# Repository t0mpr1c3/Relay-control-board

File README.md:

Relay-control-board
===================

Control board for NAIS JSM1A or Songle SRD NO relays on Dangerous Prototypes DP5031 standard PCB size.

Derived from Sparkfun Electronics COM-11041 designed by N. Seidle and Joel Bartlett.

The component values are designed for VCC = 5 VDC. For VCC = 12 VDC, use R2 = 2.2K and R4 = 3.3K.

Released under Creative Commons Attribution Share-Alike 3.0 License. http://creativecommons.org/licenses/by-sa/3.0

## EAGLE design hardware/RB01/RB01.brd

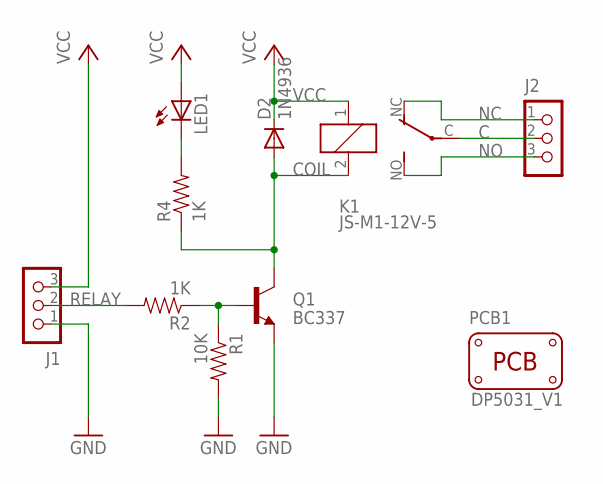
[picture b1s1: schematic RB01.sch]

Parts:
D2: 1N4936; DO41-10
J1, J2: CON_TERMINAL_BLOCK_03-5MM; TERMINAL_BLOCK_3P_5
K1: JS-M1-12V-5; JS-M; MPN JSM1-12V-5
LED1: LED-3MM
PCB1: PCB_DP_RECTANGLE-31X50; DP5031_V1
Q1: BC337; TO92
R1: 10K; AXIAL-0.3
R2, R4: 1K; AXIAL-0.3

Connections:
C: J2.2, K1.C
COIL: D2.A, K1.2, Q1.3 (C), R4.P$1 (1)
GND: J1.1, Q1.1 (E), R1.P$2 (2)
unnamed: Q1.2 (B), R1.P$1 (1), R2.P$1 (1)
unnamed: LED1.K (C), R4.P$2 (2)
NC: J2.1, K1.NC (O)
NO: J2.3, K1.NO (S)
RELAY: J1.2, R2.P$2 (2)
VCC: D2.C, J1.3, K1.1, LED1.A

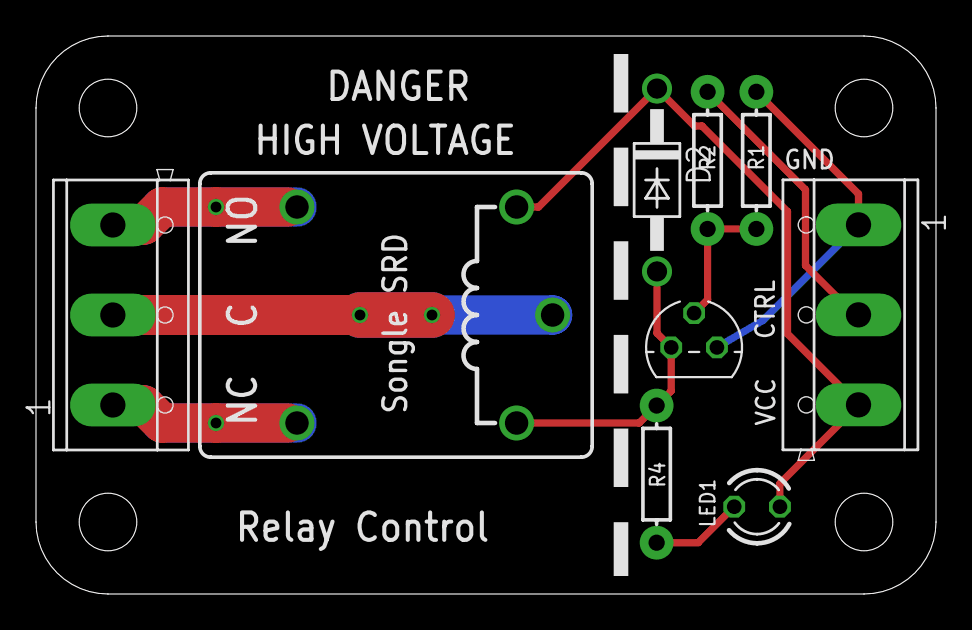
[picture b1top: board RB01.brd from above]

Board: 4 copper layers, 50.0 x 31.0 mm, 11 parts (1 on the bottom side), 9 nets.

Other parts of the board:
U$2: OSHW-LOGO-S

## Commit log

2013-11-23 RB01 first draft
2013-11-23 gerbers
2013-11-23 BC337s instead of BC546s
2013-11-24 Magic Smoke logo
2013-11-25 tweak gerbers
2013-11-26 JS-M1 relay package
2013-11-27 reorganize folders
2013-12-03 2mm clearance
2013-12-04 hot traces on bottom only
2013-12-09 faster higher-power diode closer to coil

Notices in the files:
hardware/RB01/RB01.brd:
CC BY-SA 3.0
